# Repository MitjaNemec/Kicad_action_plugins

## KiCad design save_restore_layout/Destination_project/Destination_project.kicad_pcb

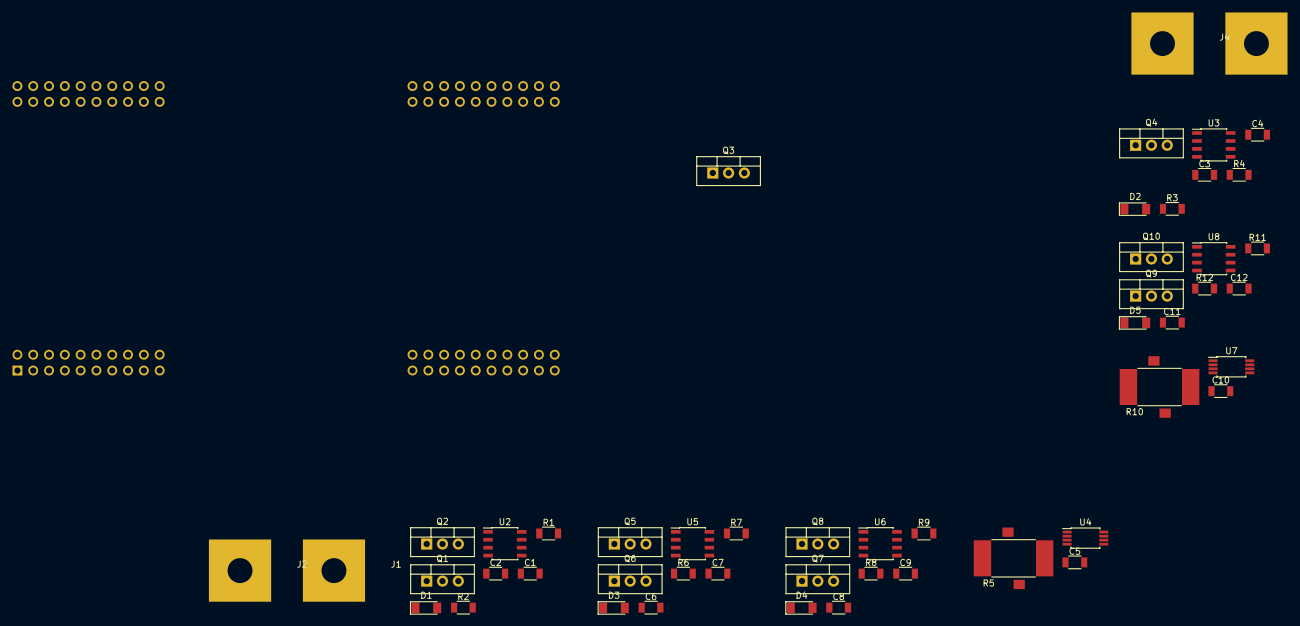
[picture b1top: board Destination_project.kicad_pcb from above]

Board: 2 copper layers, 51 parts (0 on the bottom side), 49 nets, no tracks yet.

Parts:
C1, C2, C3, C4, C6, C7, C8, C9, C11, C12: 100n; C1206M
C5, C10: C1206; C1206M
D1, D2, D3, D4, D5: LL4148; D_MiniMELF
J1, J2, J3, J4: Pusa_4mm
Q1, Q2, Q3, Q4, Q5, Q6, Q7, Q8, Q9, Q10: CSD19531KCS; TO-220
R1, R2, R3, R4, R6, R7, R8, R9, R11, R12: 22R; R1206M
R5, R10: R_Shunt; RM
U1: LAUNCHXL-F28379D; 28379D_launchpad
U2, U3, U5, U6, U8: IR2181; SO8
U4, U7: INA240; TSSOP-8_4.4x3mm_P0.65mm

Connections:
+3V3: C5.1, C10.1, U1.1, U1.41, U4.5, U4.6, U7.5, U7.6
+5V: U1.21, U1.61
+15V: C1.1, C3.1, C6.1, C8.1, C11.1, D1.2, D2.2, D3.2, D4.2, D5.2, U2.5, U3.5, U5.5, U6.5, U8.5
+VDC: Q1.2, Q3.2, Q5.2, Q7.2, Q9.2
-VDC: C1.2, C3.2, C5.2, C6.2, C8.2, C10.2, C11.2, Q2.3, Q4.3, Q6.3, Q8.3, Q10.3, U1.20, U1.22, U1.60, U1.62, U2.3, U3.3, U4.4, U4.7, U5.3, U6.3, U7.4, U7.7, U8.3
/Leg 2/Current: U1.63, U7.8
/Leg 2/Power-/OUT: C12.2, J4.1, Q9.3, Q10.2, U8.6
/Leg 2/QH: U1.80, U6.1, U8.2
/Leg 2/QL: U1.79, U6.2, U8.1
/Leg 2/Sensor/IN: C9.2, Q7.3, Q8.2, R10.4, U6.6
/Leg 2/Sensor/OUT: J3.1, R10.1
/Leg/Current: U1.24, U4.8
/Leg/Power-/OUT: C7.2, J2.1, Q5.3, Q6.2, U5.6
/Leg/QH: U1.40, U3.1, U5.2
/Leg/QL: U1.39, U3.2, U5.1
/Leg/Sensor/IN: C4.2, Q3.3, Q4.2, R5.4, U3.6
/Leg/Sensor/OUT: J1.1, R5.1
/power/OUT: C2.2, Q1.3, Q2.2, U2.6
/power/QH: U1.38, U2.1
/power/Ql: U1.37, U2.2
unnamed: C2.1, D1.1, U2.8
unnamed: C4.1, D2.1, U3.8
unnamed: C7.1, D3.1, U5.8
unnamed: C9.1, D4.1, U6.8
unnamed: C12.1, D5.1, U8.8
unnamed: Q1.1, R1.2
unnamed: Q2.1, R2.2
unnamed: Q3.1, R3.2
unnamed: Q4.1, R4.2
unnamed: Q5.1, R6.2
unnamed: Q6.1, R7.2
unnamed: Q7.1, R8.2
unnamed: Q8.1, R9.2
unnamed: Q9.1, R11.2
unnamed: Q10.1, R12.2
unnamed: R1.1, U2.7
unnamed: R2.1, U2.4
unnamed: R3.1, U3.7
unnamed: R4.1, U3.4
unnamed: R5.2, U4.3
unnamed: R5.3, U4.2
unnamed: R6.1, U5.7
unnamed: R7.1, U5.4
unnamed: R8.1, U6.7
unnamed: R9.1, U6.4
unnamed: R10.2, U7.3
unnamed: R10.3, U7.2
unnamed: R11.1, U8.7
unnamed: R12.1, U8.4

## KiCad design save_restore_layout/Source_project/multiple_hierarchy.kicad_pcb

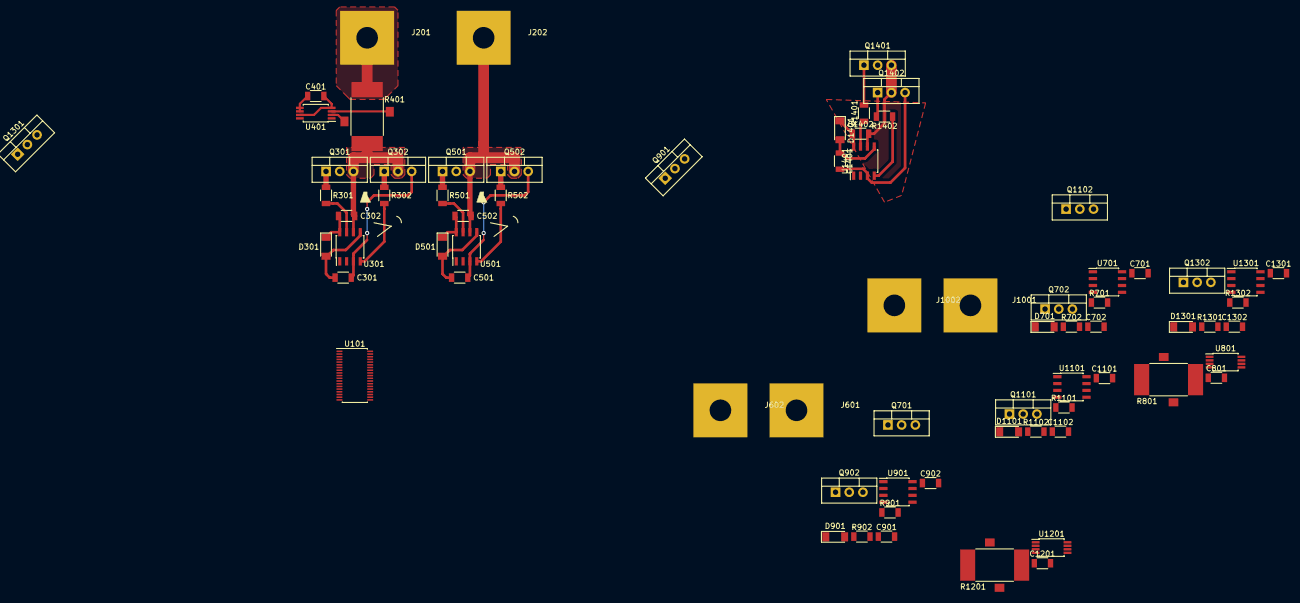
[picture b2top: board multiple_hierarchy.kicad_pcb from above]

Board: 2 copper layers, 72 parts (0 on the bottom side), 66 nets.

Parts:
C301, C302, C501, C502, C701, C702, C901, C902, C1101, C1102, C1301, C1302, C1401, C1402: 100n; C1206M
C401, C801, C1201: C1206; C1206M
D301, D501, D701, D901, D1101, D1301, D1401: LL4148; D_MiniMELF
J201, J202, J601, J602, J1001, J1002: Pusa_4mm
Q301, Q302, Q501, Q502, Q701, Q702, Q901, Q902, Q1101, Q1102, Q1301, Q1302, Q1401, Q1402: CSD19531KCS; TO-220
R301, R302, R501, R502, R701, R702, R901, R902, R1101, R1102, R1301, R1302, R1401, R1402: 22R; R1206M
R401, R801, R1201: R_Shunt; RM
U101: TMS320F28027DA; TSSOP-38_4.4x9.7mm_P0.5mm
U301, U501, U701, U901, U1101, U1301, U1401: IR2181; SO8
U401, U801, U1201: INA240; TSSOP-8_4.4x3mm_P0.65mm

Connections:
+3V3: C401.1, C801.1, C1201.1, U101.4, U101.22, U401.5, U401.6, U801.5, U801.6, U1201.5, U1201.6
+15V: C301.1, C501.1, C701.1, C901.1, C1101.1, C1301.1, C1401.1, D301.2, D501.2, D701.2, D901.2, D1101.2, D1301.2, D1401.2, U301.5, U501.5, U701.5, U901.5, U1101.5, U1301.5, U1401.5
+VDC: Q301.2, Q501.2, Q701.2, Q901.2, Q1101.2, Q1301.2, Q1401.2
-VDC: C301.2, C401.2, C501.2, C701.2, C801.2, C901.2, C1101.2, C1201.2, C1301.2, C1401.2, Q302.3, Q502.3, Q702.3, Q902.3, Q1102.3, Q1302.3, Q1402.3, U101.2, U101.12, U101.23, U301.3, U401.4, U401.7, U501.3, U701.3, U801.4, U801.7, U901.3, U1101.3, U1201.4, U1201.7, U1301.3, U1401.3
/Leg1/Current: U101.21, U401.8
/Leg1/Power-/OUT: C502.2, J202.1, Q501.3, Q502.2, U501.6
/Leg1/QH: U101.37, U301.1, U501.2
/Leg1/QL: U101.36, U301.2, U501.1
/Leg1/Sensor/IN: C302.2, Q301.3, Q302.2, R401.4, U301.6
/Leg1/Sensor/OUT: J201.1, R401.1
/Leg2/Current: U101.20, U801.8
/Leg2/Power-/OUT: C902.2, J602.1, Q901.3, Q902.2, U901.6
/Leg2/QH: U101.5, U701.1, U901.2
/Leg2/QL: U101.6, U701.2, U901.1
/Leg2/Sensor/IN: C702.2, Q701.3, Q702.2, R801.4, U701.6
/Leg2/Sensor/OUT: J601.1, R801.1
/Leg3/Current: U101.19, U1201.8
/Leg3/Power-/OUT: C1302.2, J1002.1, Q1301.3, Q1302.2, U1301.6
/Leg3/QH: U101.7, U1101.1, U1301.2
/Leg3/QL: U101.8, U1101.2, U1301.1
/Leg3/Sensor/IN: C1102.2, Q1101.3, Q1102.2, R1201.4, U1101.6
/Leg3/Sensor/OUT: J1001.1, R1201.1
/Power_extra/OUT: C1402.2, Q1401.3, Q1402.2, U1401.6
/Power_extra/QH: U101.9, U1401.1
/Power_extra/Ql: U101.10, U1401.2
unnamed: C302.1, D301.1, U301.8
unnamed: C502.1, D501.1, U501.8
unnamed: C702.1, D701.1, U701.8
unnamed: C902.1, D901.1, U901.8
unnamed: C1102.1, D1101.1, U1101.8
unnamed: C1302.1, D1301.1, U1301.8
unnamed: C1402.1, D1401.1, U1401.8
unnamed: Q301.1, R301.2
unnamed: Q302.1, R302.2
unnamed: Q501.1, R501.2
unnamed: Q502.1, R502.2
unnamed: Q701.1, R701.2
unnamed: Q702.1, R702.2
unnamed: Q901.1, R901.2
unnamed: Q902.1, R902.2
unnamed: Q1101.1, R1101.2
unnamed: Q1102.1, R1102.2
unnamed: Q1301.1, R1301.2
unnamed: Q1302.1, R1302.2
unnamed: Q1401.1, R1401.2
unnamed: Q1402.1, R1402.2
unnamed: R301.1, U301.7
unnamed: R302.1, U301.4
unnamed: R401.2, U401.3
unnamed: R401.3, U401.2
unnamed: R501.1, U501.7
unnamed: R502.1, U501.4
unnamed: R701.1, U701.7
unnamed: R702.1, U701.4
unnamed: R801.2, U801.3
unnamed: R801.3, U801.2
unnamed: R901.1, U901.7
unnamed: R902.1, U901.4
unnamed: R1101.1, U1101.7
unnamed: R1102.1, U1101.4
unnamed: R1201.2, U1201.3
unnamed: R1201.3, U1201.2
unnamed: R1301.1, U1301.7
unnamed: R1302.1, U1301.4
unnamed: R1401.1, U1401.7
unnamed: R1402.1, U1401.4

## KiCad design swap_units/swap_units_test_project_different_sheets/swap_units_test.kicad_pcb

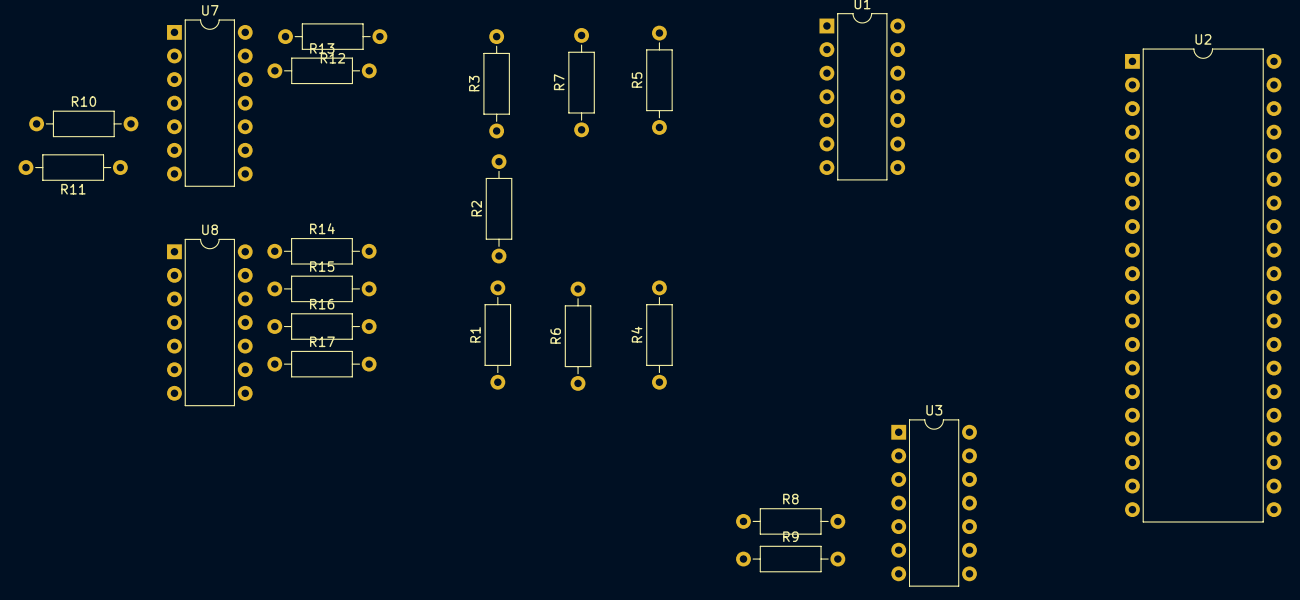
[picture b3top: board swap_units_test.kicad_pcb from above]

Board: 2 copper layers, 22 parts (0 on the bottom side), 20 nets, no tracks yet.

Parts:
R1, R2, R3, R4, R5, R6, R7, R8, R9, R10, R11, R12, R13, R14, R15, R16, R17: R; R_Axial_DIN0207_L6.3mm_D2.5mm_P10.16mm_Horizontal
U1, U3, U7, U8: LM324; DIP-14_W7.62mm
U2: PIC18F452-IP; DIP-40_W15.24mm

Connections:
+5V: R1.1, R4.1, R6.1, R8.1, R10.1, R12.1, R14.1, R16.1, U1.4, U2.11, U2.32
/Level1/Level2b/out_level_2: U3.13, U3.14
/Level1/Level3a/out_level_1: U7.13, U7.14
/Level1/Level3a/out_level_2: U7.6, U7.7
/Level1/Level3b/out_level_1: U8.13, U8.14
/Level1/Level3b/out_level_2: U8.6, U8.7
/Level1/out_level_1: U1.13, U1.14, U2.2
/Level1/out_level_2: U1.8, U1.9, U2.3
GND: R3.2, R5.2, R7.2, R9.2, R11.2, R13.2, R15.2, R17.2, U1.11, U2.12, U2.31
unnamed: R1.2, R2.1, U1.3
unnamed: R2.2, R3.1, U1.5
unnamed: R4.2, R5.1, U1.12
unnamed: R6.2, R7.1, U1.10
unnamed: R8.2, R9.1, U3.12
unnamed: R10.2, R11.1, U7.5
unnamed: R12.2, R13.1, U7.12
unnamed: R14.2, R15.1, U8.5
unnamed: R16.2, R17.1, U8.12
unnamed: U1.1, U1.2, U2.4
unnamed: U1.6, U1.7, U2.5
